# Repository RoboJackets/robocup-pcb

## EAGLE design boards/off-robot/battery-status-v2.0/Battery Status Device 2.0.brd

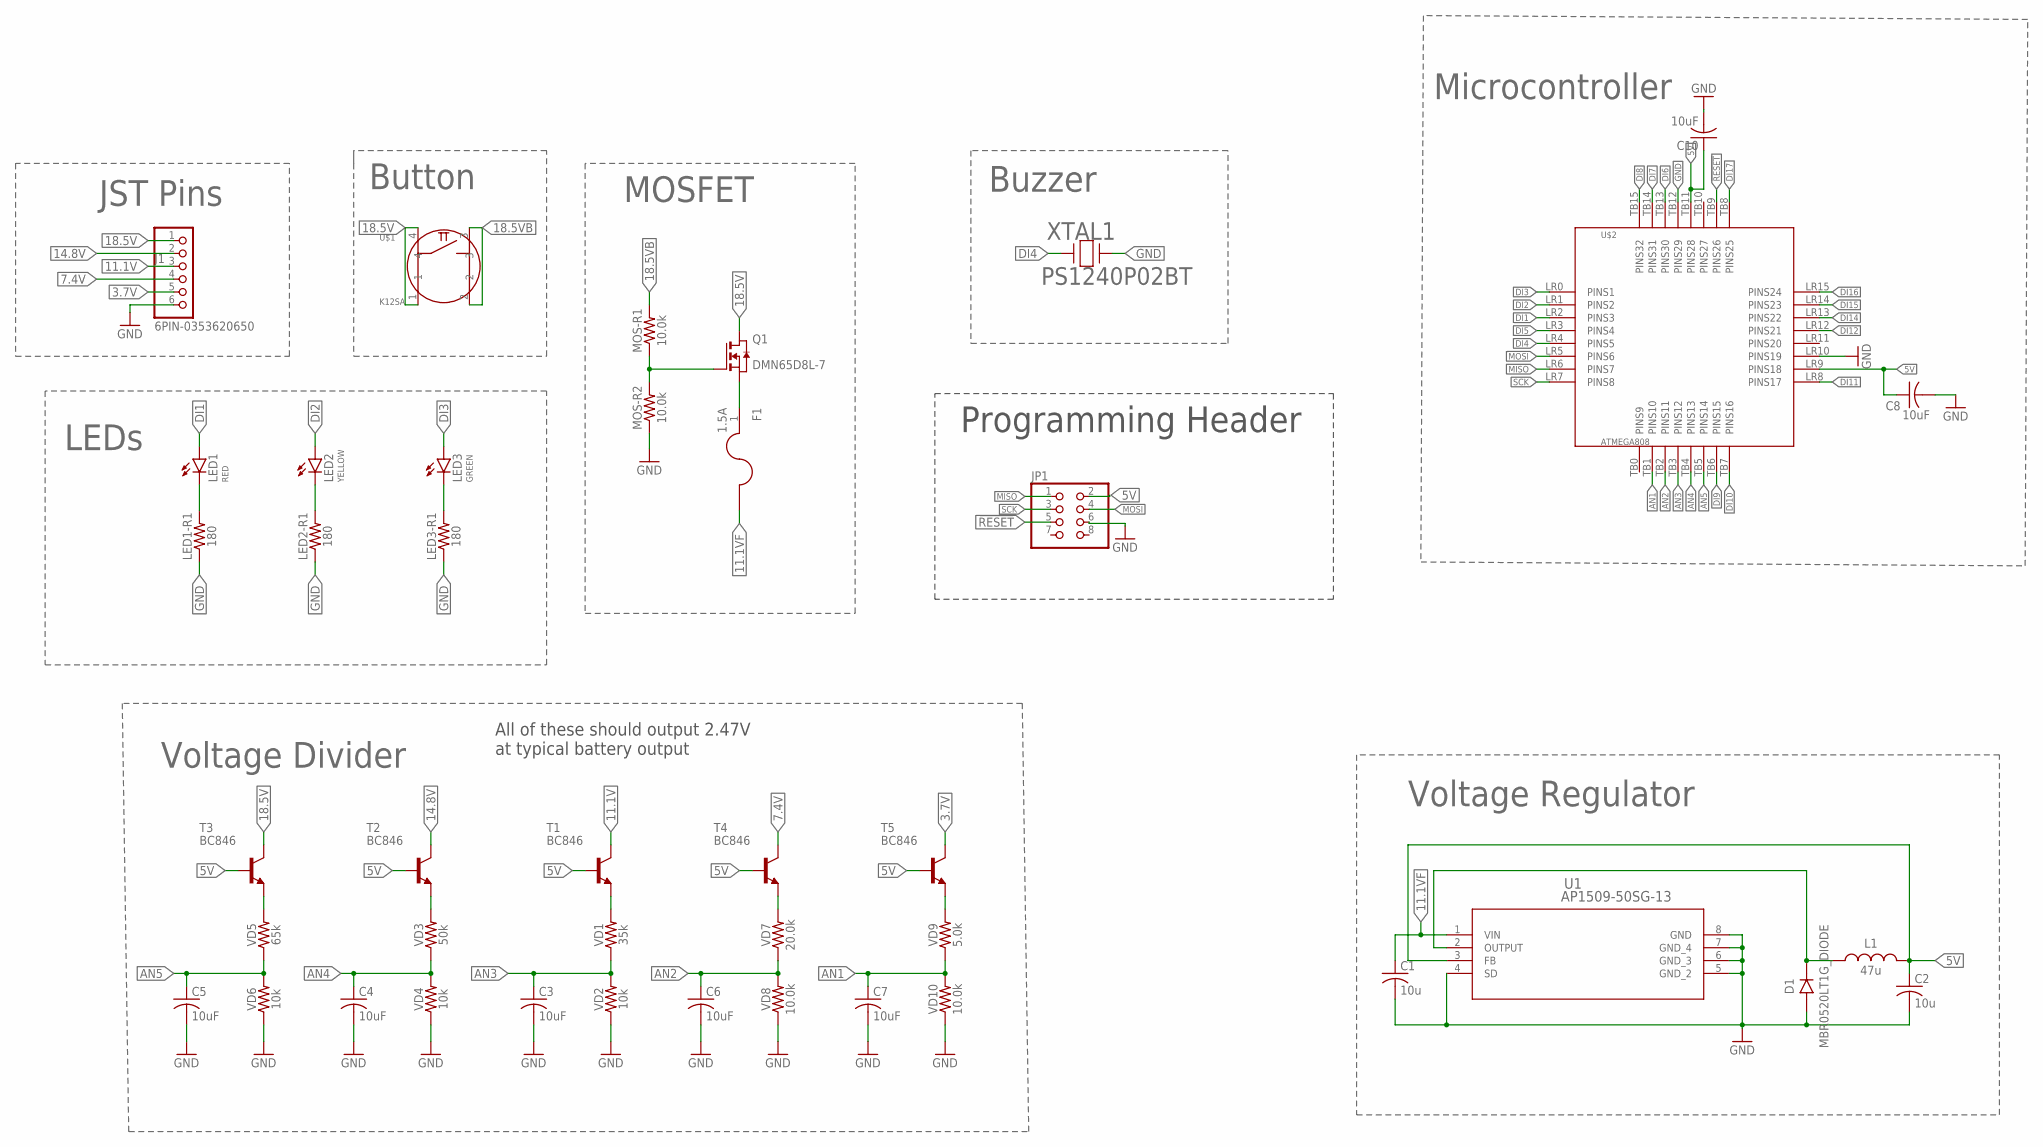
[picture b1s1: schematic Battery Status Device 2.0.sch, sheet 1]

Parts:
C1, C2: 10u; C0805
C3, C4, C5, C6, C7, C8, C10: 10uF; C0805
D1: MBR0520LT1G_DIODE; SOD-123
F1: 1.5A; F1206
J1: 6PIN-0353620650; 0353620650
JP1: PINHD-2X4; 2X04
L1: 47u; 0805
LED1: RED; LED5MM
LED1-R1, LED2-R1, LED3-R1: 180; 0603
LED2: YELLOW; LED5MM
LED3: GREEN; LED5MM
MOS-R1, MOS-R2: 10.0k; 0603
Q1: DMN65D8L-7; SOT-23-3
T1, T2, T3, T4, T5: BC846; SOT23
U1: AP1509-50SG-13; SOP-8L_DIO
U$1: K12SA
U$2: ATMEGA808
VD1: 35k; 0603
VD2, VD4, VD6: 10k; 0603
VD3: 50k; 0603
VD5: 65k; 0603
VD7: 20.0k; 0603
VD8, VD10: 10.0k; 0603
VD9: 5.0k; 0603
XTAL1: PS1240P02BT; XTAL_PS1240P02BT_TDK

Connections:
3.7V: J1.5, T5.3 (C)
5V: C2.1, C8.1, C10.1, JP1.2, L1.2, T1.1 (B), T2.1 (B), T3.1 (B), T4.1 (B), T5.1 (B), U1.3 (FB), U$2.LR9 (PINS18), U$2.TB11 (PINS28); also elsewhere on the board
7.4V: J1.4, T4.3 (C)
11.1V: J1.3, T1.3 (C)
11.1VF: C1.1, F1.2, U1.1 (VIN)
14.8V: J1.2, T2.3 (C)
18.5V: J1.1, Q1.3 (D), T3.3 (C), U$1.1, U$1.4
18.5VB: MOS-R1.2, U$1.2, U$1.3
!RESET!: JP1.5, U$2.TB9 (PINS26)
AN1: C7.1, U$2.TB1 (PINS10), VD9.1, VD10.2
AN2: C6.1, U$2.TB2 (PINS11), VD7.1, VD8.2
AN3: C3.1, U$2.TB3 (PINS12), VD1.1, VD2.2
AN4: C4.1, U$2.TB4 (PINS13), VD3.1, VD4.2
AN5: C5.1, U$2.TB5 (PINS14), VD5.1, VD6.2
DI1: LED1.A, U$2.LR2 (PINS3)
DI2: LED2.A, U$2.LR1 (PINS2)
DI3: LED3.A, U$2.LR0 (PINS1)
DI4: U$2.LR4 (PINS5), XTAL1.1
DI5: U$2.LR3 (PINS4); also elsewhere on the board
DI6: U$2.TB13 (PINS30); also elsewhere on the board
DI7: U$2.TB14 (PINS31); also elsewhere on the board
DI8: U$2.TB15 (PINS32); also elsewhere on the board
DI9: U$2.TB6 (PINS15); also elsewhere on the board
DI10: U$2.TB7 (PINS16); also elsewhere on the board
DI11: U$2.LR8 (PINS17); also elsewhere on the board
DI12: U$2.LR12 (PINS21); also elsewhere on the board
DI14: U$2.LR13 (PINS22); also elsewhere on the board
DI15: U$2.LR14 (PINS23); also elsewhere on the board
DI16: U$2.LR15 (PINS24); also elsewhere on the board
DI17: U$2.TB8 (PINS25); also elsewhere on the board
GND: C1.2, C2.2, C3.2, C4.2, C5.2, C6.2, C7.2, C8.2, C10.2, D1.2 (A), J1.6, JP1.6, LED1-R1.1, LED2-R1.1, LED3-R1.1, MOS-R2.1, U1.4 (SD), U1.5 (GND_2), U1.6 (GND_3), U1.7 (GND_4), U1.8 (GND), U$2.LR10 (PINS19), U$2.TB12 (PINS29), VD2.1, VD4.1, VD6.1, VD8.1, VD10.1, XTAL1.2; also elsewhere on the board
MISO: JP1.1, U$2.LR6 (PINS7)
MOSI: JP1.4, U$2.LR5 (PINS6)
unnamed: D1.1 (C), L1.1, U1.2 (OUTPUT)
unnamed: LED1.K (C), LED1-R1.2
unnamed: LED2.K (C), LED2-R1.2
unnamed: LED3.K (C), LED3-R1.2
unnamed: T5.2 (E), VD9.2
unnamed: T4.2 (E), VD7.2
unnamed: T1.2 (E), VD1.2
unnamed: MOS-R1.1, MOS-R2.2, Q1.1 (G)
unnamed: T2.2 (E), VD3.2
unnamed: F1.1, Q1.2 (S)
unnamed: T3.2 (E), VD5.2
SCK: JP1.3, U$2.LR7 (PINS8)

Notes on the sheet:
Microcontroller
Voltage Regulator
Voltage Divider
JST Pins
Button
Buzzer
LEDs
Programming Header
MOSFET
All of these should output 2.47V at typical battery output

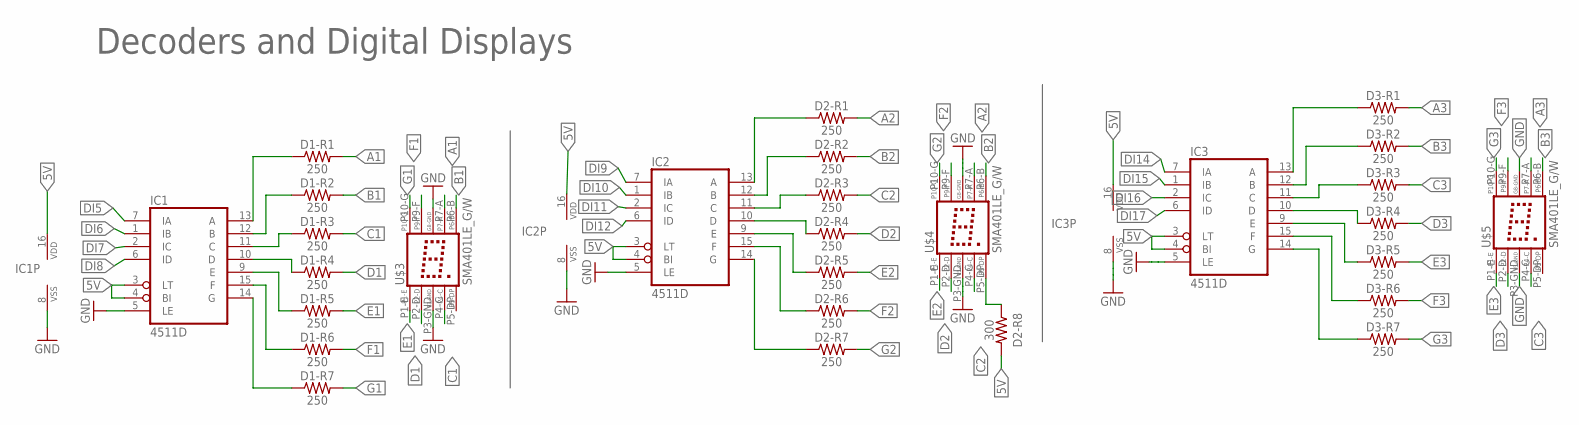
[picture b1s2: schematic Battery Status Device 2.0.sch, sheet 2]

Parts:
D1-R1, D1-R2, D1-R3, D1-R4, D1-R5, D1-R6, D1-R7, D2-R1, D2-R2, D2-R3, D2-R4, D2-R5, D2-R6, D2-R7, D3-R1, D3-R2, D3-R3, D3-R4, D3-R5, D3-R6, D3-R7: 250; 0603
D2-R8: 300; 0603
IC1, IC2, IC3: 4511D; SO16
U$3, U$4, U$5: SMA401LE_G/W

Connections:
5V: D2-R8.2, IC1.3 (LT), IC1.4 (BI), IC1.16 (VDD), IC2.3 (LT), IC2.4 (BI), IC2.16 (VDD), IC3.3 (LT), IC3.4 (BI), IC3.16 (VDD); also elsewhere on the board
A1: D1-R1.2, U$3.P7-A
A2: D2-R1.2, U$4.P7-A
A3: D3-R1.2, U$5.P7-A
B1: D1-R2.2, U$3.P6-B
B2: D2-R2.2, U$4.P6-B
B3: D3-R2.2, U$5.P6-B
C1: D1-R3.2, U$3.P4-C
C2: D2-R3.2, U$4.P4-C
C3: D3-R3.2, U$5.P4-C
D1: D1-R4.2, U$3.P2-D
D2: D2-R4.2, U$4.P2-D
D3: D3-R4.2, U$5.P2-D
DI5: IC1.7 (IA); also elsewhere on the board
DI6: IC1.1 (IB); also elsewhere on the board
DI7: IC1.2 (IC); also elsewhere on the board
DI8: IC1.6 (ID); also elsewhere on the board
DI9: IC2.7 (IA); also elsewhere on the board
DI10: IC2.1 (IB); also elsewhere on the board
DI11: IC2.2 (IC); also elsewhere on the board
DI12: IC2.6 (ID); also elsewhere on the board
DI14: IC3.7 (IA); also elsewhere on the board
DI15: IC3.1 (IB); also elsewhere on the board
DI16: IC3.2 (IC); also elsewhere on the board
DI17: IC3.6 (ID); also elsewhere on the board
E1: D1-R5.2, U$3.P1-E
E2: D2-R5.2, U$4.P1-E
E3: D3-R5.2, U$5.P1-E
F1: D1-R6.2, U$3.P9-F
F2: D2-R6.2, U$4.P9-F
F3: D3-R6.2, U$5.P9-F
G1: D1-R7.2, U$3.P10-G
G2: D2-R7.2, U$4.P10-G
G3: D3-R7.2, U$5.P10-G
GND: IC1.5 (LE), IC1.8 (VSS), IC2.5 (LE), IC2.8 (VSS), IC3.5 (LE), IC3.8 (VSS), U$3.P3-GND, U$3.P8-GND, U$4.P3-GND, U$4.P8-GND, U$5.P3-GND, U$5.P8-GND; also elsewhere on the board
unnamed: D1-R1.1, IC1.13 (A)
unnamed: D1-R2.1, IC1.12 (B)
unnamed: D1-R3.1, IC1.11 (C)
unnamed: D1-R4.1, IC1.10 (D)
unnamed: D1-R6.1, IC1.15 (F)
unnamed: D1-R5.1, IC1.9 (E)
unnamed: D1-R7.1, IC1.14 (G)
unnamed: D2-R1.1, IC2.13 (A)
unnamed: D2-R2.1, IC2.12 (B)
unnamed: D2-R3.1, IC2.11 (C)
unnamed: D2-R4.1, IC2.10 (D)
unnamed: D2-R5.1, IC2.9 (E)
unnamed: D2-R6.1, IC2.15 (F)
unnamed: D2-R7.1, IC2.14 (G)
unnamed: D3-R1.1, IC3.13 (A)
unnamed: D3-R2.1, IC3.12 (B)
unnamed: D3-R3.1, IC3.11 (C)
unnamed: D3-R4.1, IC3.10 (D)
unnamed: D3-R5.1, IC3.9 (E)
unnamed: D3-R6.1, IC3.15 (F)
unnamed: D3-R7.1, IC3.14 (G)
unnamed: D2-R8.1, U$4.P5-DP

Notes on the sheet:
Decoders and Digital Displays

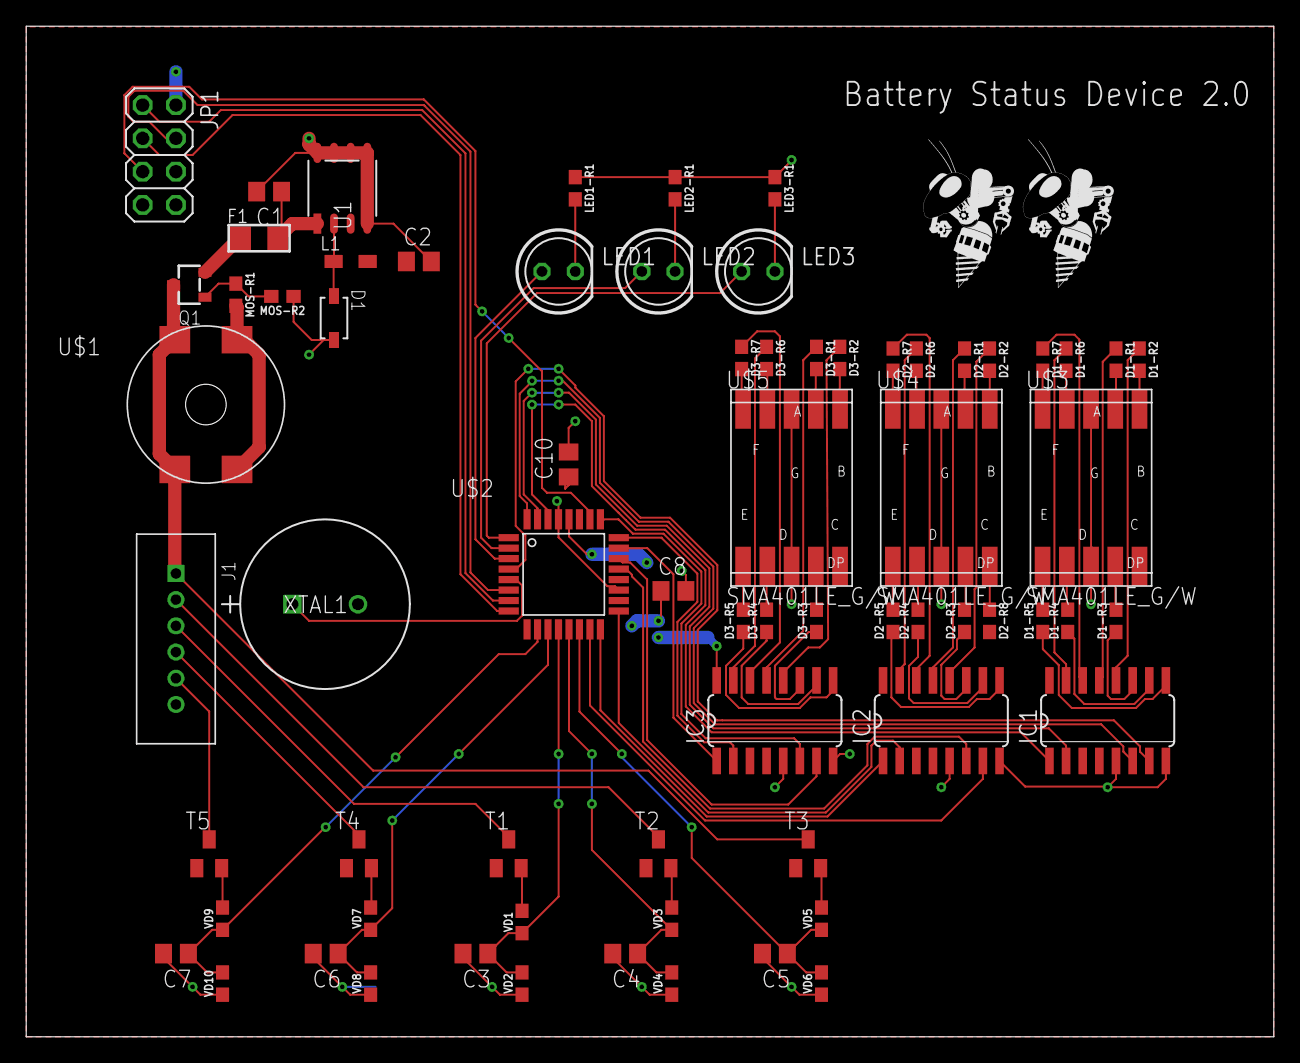
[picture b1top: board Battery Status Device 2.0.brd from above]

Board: 2 copper layers, 95.2 x 77.1 mm, 72 parts (0 on the bottom side), 88 nets.

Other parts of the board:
U$6, U$7: ROBOBUZZ_0.6X

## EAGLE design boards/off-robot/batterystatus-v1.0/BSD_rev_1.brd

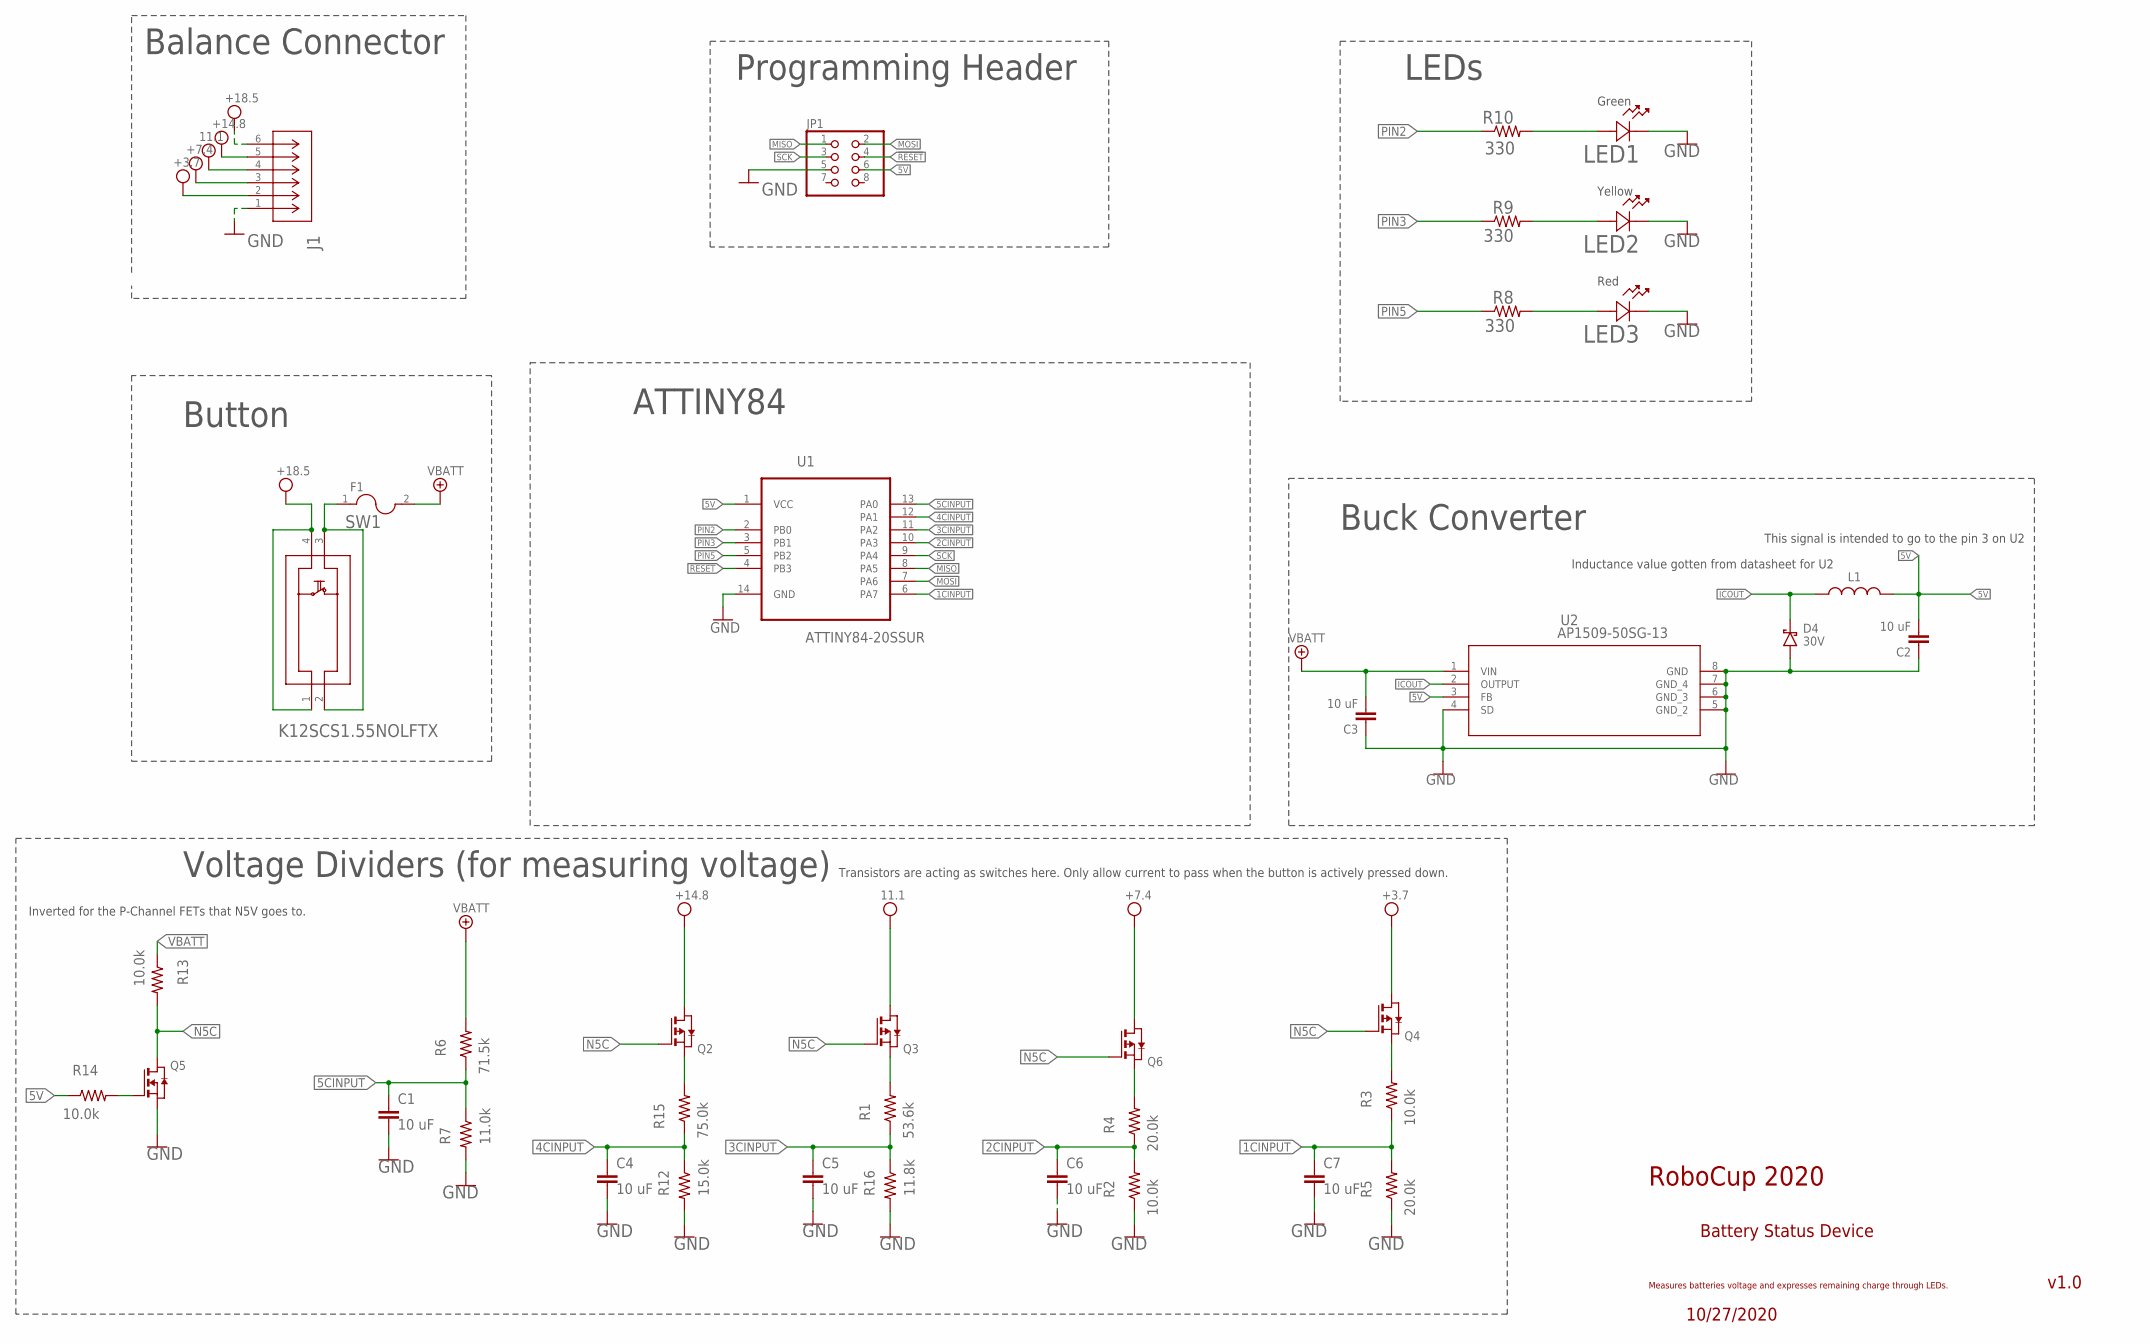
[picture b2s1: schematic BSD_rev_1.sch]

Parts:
C1, C2, C3, C4, C5, C6, C7: 10 uF; C0603
D4: 30V; POWERDI-123
F1: 0698Q5000-01; FUSE_0698Q5000-01
J1: B6B-XH-A(LF)(SN); CONN_B6B-XH-A(LF)(SN)_JST
JP1: PINHD-2X4; 2X04
L1: 48470SC
LED1, LED2, LED3: SLR-56VC3F; LED_SLR-56_ROM
Q2, Q3, Q4, Q6: SOT233; SOT-23_DIO-L
Q5: LND150K1-G; SOT-23-3
R1: 53.6k; R0603
R2, R3, R13, R14: 10.0k; R0603
R4, R5: 20.0k; R0603
R6: 71.5k; R0603
R7: 11.0k; R0603
R8, R9, R10: 330; R0603
R12: 15.0k; R0603
R15: 75.0k; R0603
R16: 11.8k; R0603
SW1: K12SCS1.55NOLFTX
U1: ATTINY84-20SSUR; SOIC127P600X175-14N
U2: AP1509-50SG-13; SOP-8L_DIO

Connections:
1C: J1.2, Q4.3 (D)
1CINPUT: C7.2, R3.1, R5.2, U1.6 (PA7)
2C: J1.3, Q6.3 (D)
2CINPUT: C6.2, R2.2, R4.1, U1.10 (PA3)
3C: J1.4, Q3.3 (D)
3CINPUT: C5.2, R1.1, R16.1, U1.11 (PA2)
4C: J1.5, Q2.3 (D)
4CINPUT: C4.2, R12.1, R15.1, U1.12 (PA1)
5C: J1.6, SW1.1, SW1.4
5CINPUT: C1.2, R6.1, R7.1, U1.13 (PA0)
5V: C2.2, JP1.6, L1.P$2 (2), R14.1, U1.1 (VCC), U2.3 (FB)
!RESET!: JP1.4, U1.4 (PB3)
GLED: LED1.2, R10.2
GND: C1.1, C2.1, C3.1, C4.1, C5.1, C6.1, C7.1, D4.A, J1.1, JP1.5, LED1.1, LED2.1, LED3.1, Q5.3 (S), R2.1, R5.1, R7.2, R12.2, R16.2, U1.14 (GND), U2.4 (SD), U2.5 (GND_2), U2.6 (GND_3), U2.7 (GND_4), U2.8 (GND)
ICOUT: D4.C, L1.P$1 (1), U2.2 (OUTPUT)
IDK: Q5.1 (G), R14.2
MISO: JP1.1, U1.8 (PA5)
MOSI: JP1.2, U1.7 (PA6)
N5C: Q2.1 (G), Q3.1 (G), Q4.1 (G), Q5.2 (D), Q6.1 (G), R13.2
unnamed: Q6.2 (S), R4.2
unnamed: Q4.2 (S), R3.2
unnamed: Q2.2 (S), R15.2
unnamed: Q3.2 (S), R1.2
PIN2: R10.1, U1.2 (PB0)
PIN3: R9.1, U1.3 (PB1)
PIN5: R8.1, U1.5 (PB2)
RLED: LED3.2, R8.2
SCK: JP1.3, U1.9 (PA4)
VBATT: C3.2, F1.2, R6.2, R13.1, U2.1 (VIN)
VBATTB: F1.1, SW1.2, SW1.3
YLED: LED2.2, R9.2

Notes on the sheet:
RoboCup 2020
Battery Status Device
Measures batteries voltage and expresses remaining charge through LEDs.
v1.0
10/27/2020
LEDs
ATTINY84
Button
Balance Connector
Buck Converter
This signal is intended to go to the pin 3 on U2
Programming Header
Voltage Dividers (for measuring voltage)
Transistors are acting as switches here. Only allow current to pass when the button is actively pressed down.
Inductance value gotten from datasheet for U2
Green
Red
Yellow
Inverted for the P-Channel FETs that N5V goes to.

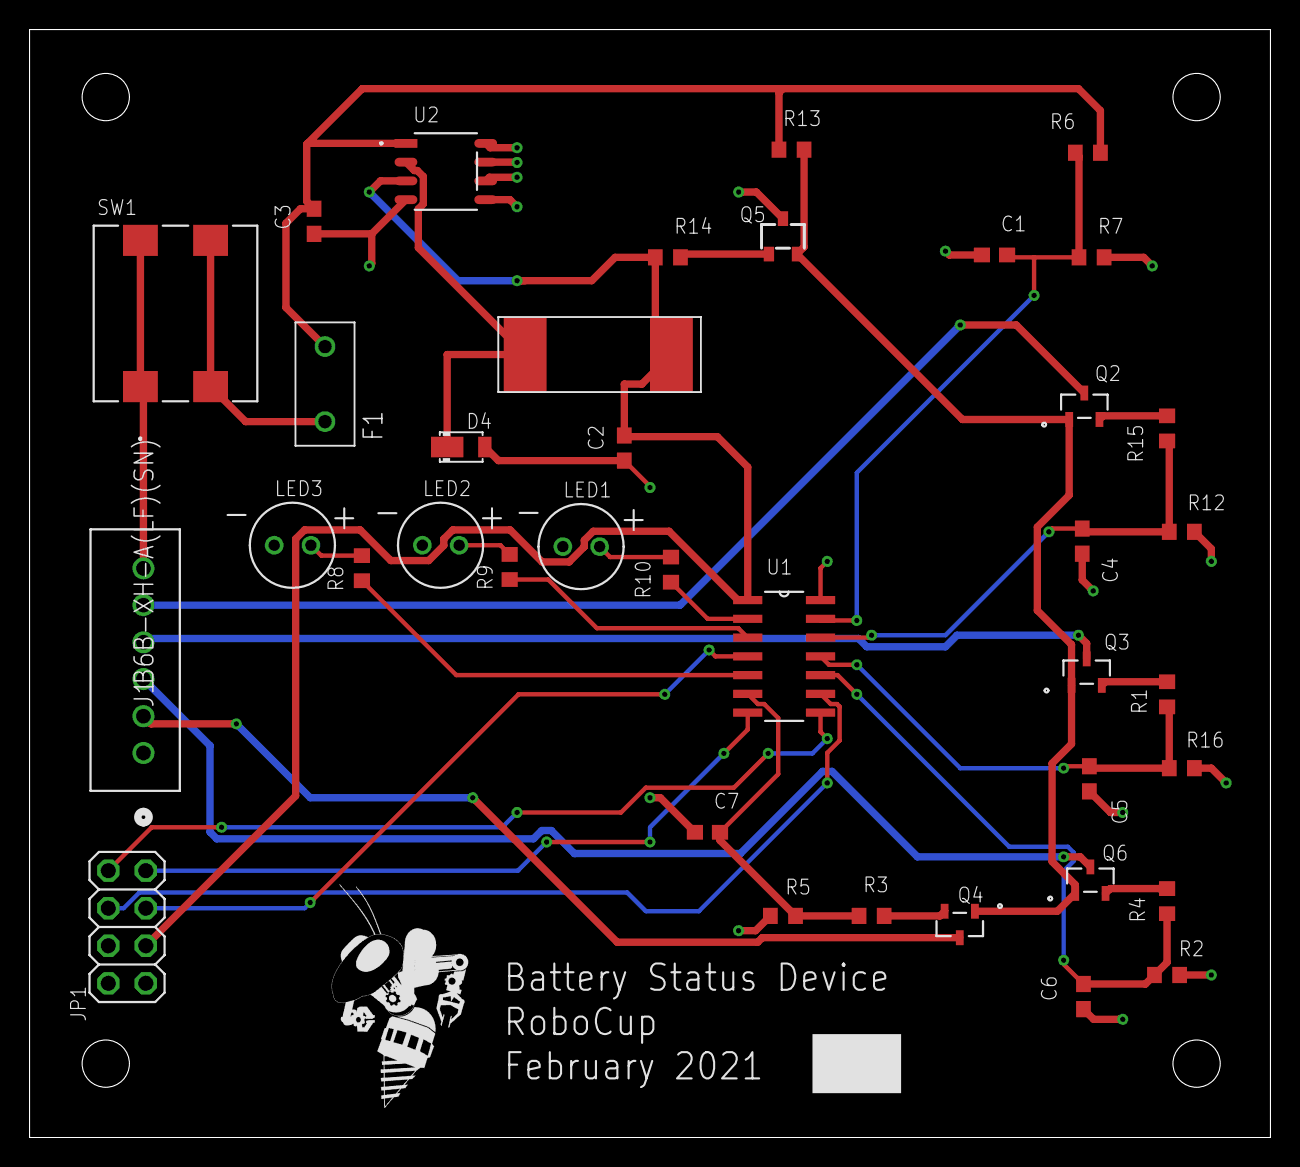
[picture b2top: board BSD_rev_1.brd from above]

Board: 2 copper layers, 84.0 x 75.0 mm, 39 parts (0 on the bottom side), 31 nets.

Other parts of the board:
U$2: ROBOBUZZ_0.8X

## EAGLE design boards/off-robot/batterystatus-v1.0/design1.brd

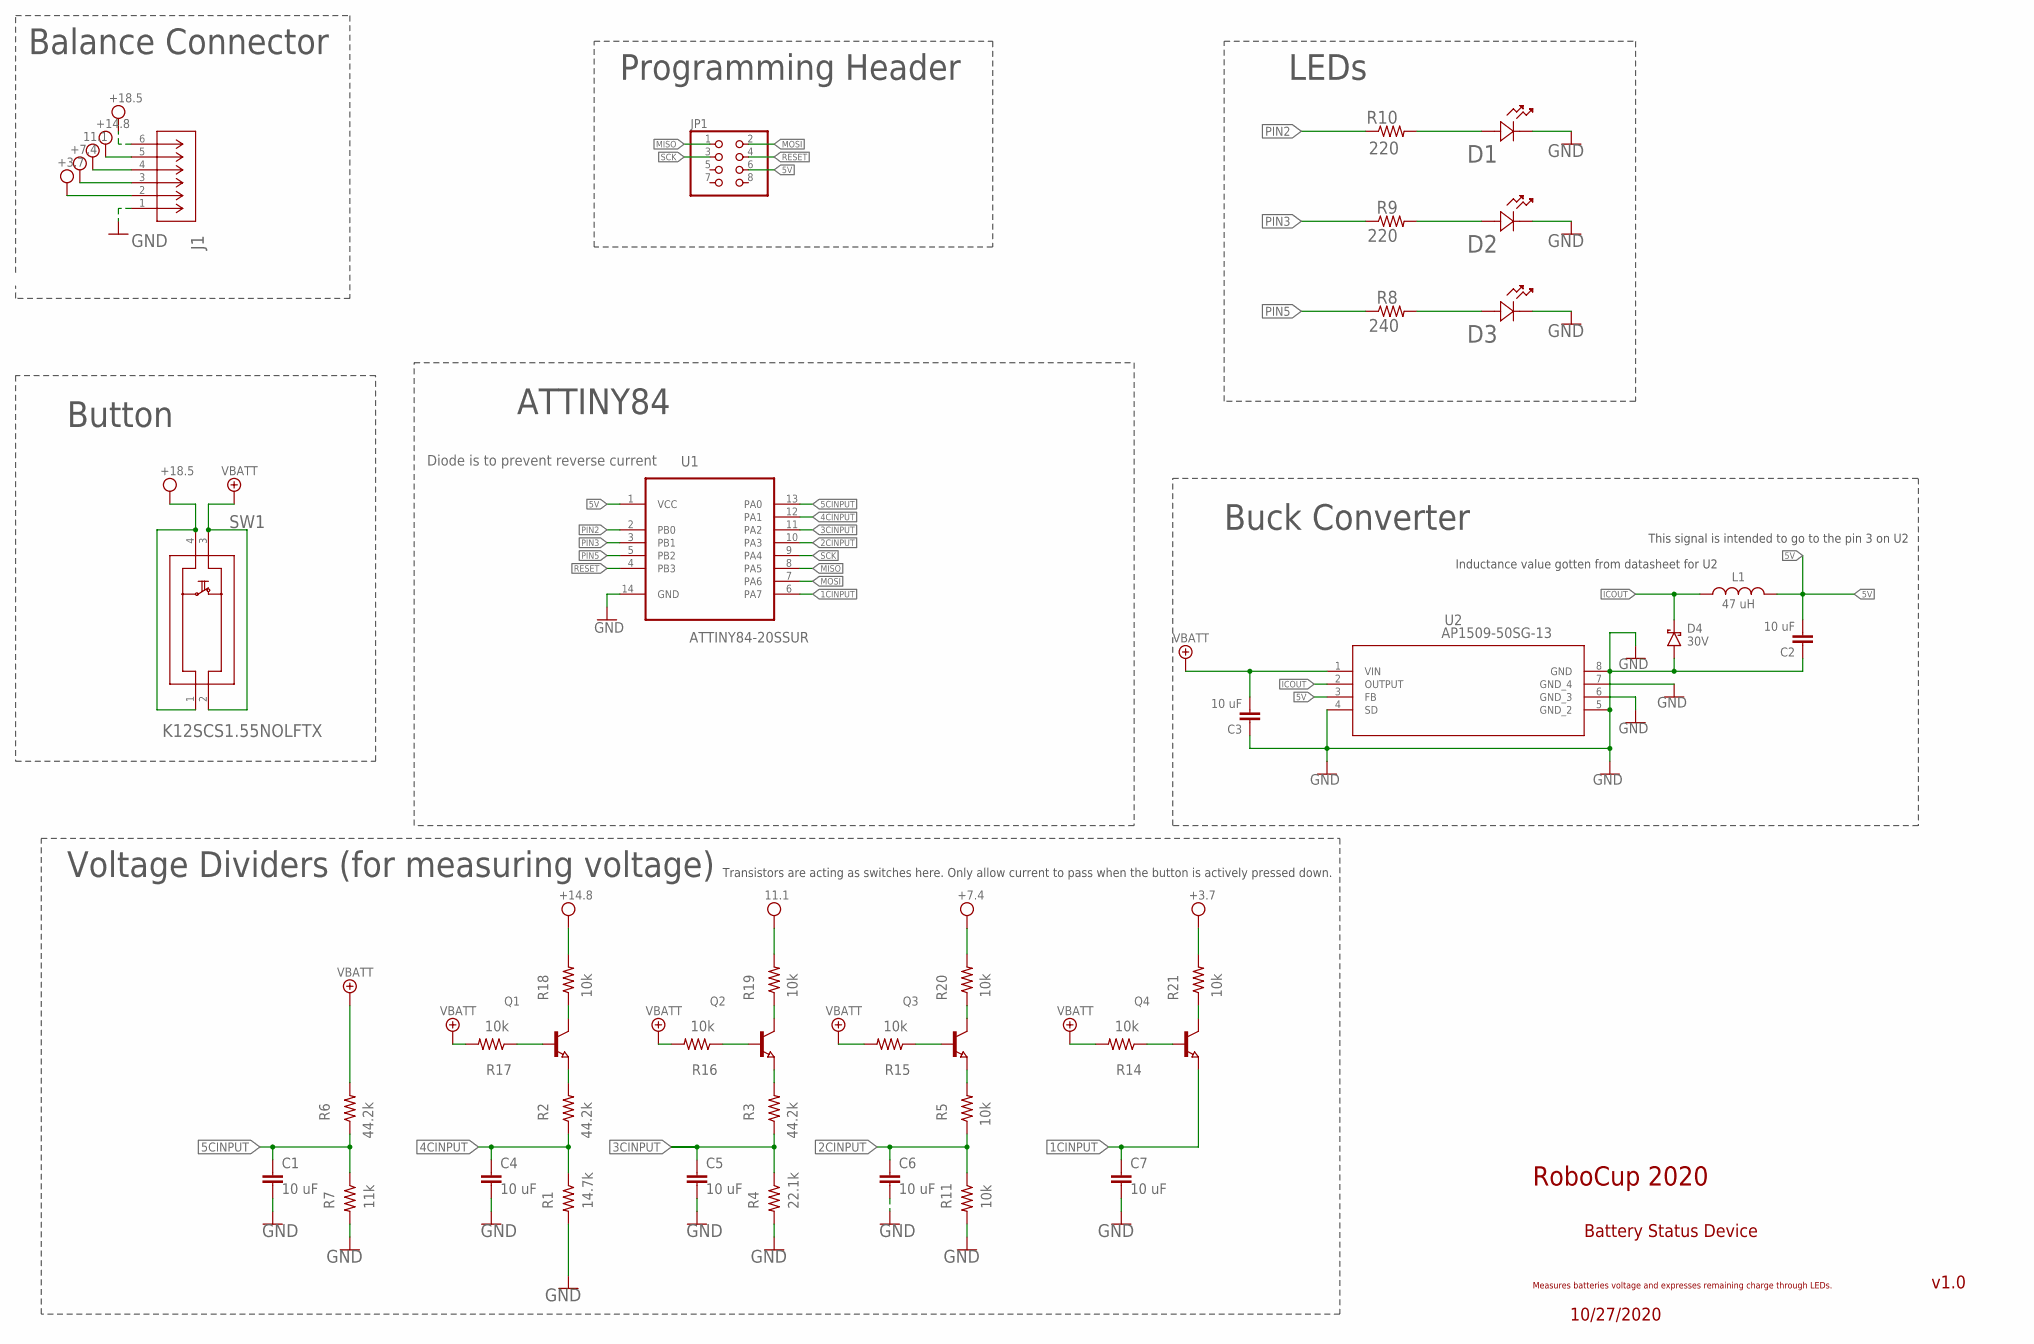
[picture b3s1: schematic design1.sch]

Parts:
C1, C2, C3, C4, C5, C6, C7: 10 uF; C0603
D1, D2, D3: SLR-56VC3F; LED_SLR-56_ROM
D4: 30V; POWERDI-123
J1: B6B-XH-A(LF)(SN); CONN_B6B-XH-A(LF)(SN)_JST
JP1: PINHD-2X4; 2X04
L1: 47 uH; 48470SC
Q1, Q2, Q3, Q4: NPN-TRANSISTOR_SOT23; SOT23
R1: 14.7k; R0603
R2, R3, R6: 44.2k; R0603
R4: 22.1k; R0603
R5, R11, R14, R15, R16, R17, R18, R19, R20, R21: 10k; R0603
R7: 11k; R0603
R8: 240; R0603
R9, R10: 220; R0603
SW1: K12SCS1.55NOLFTX
U1: ATTINY84-20SSUR; SOIC127P600X175-14N
U2: AP1509-50SG-13; SOP-8L_DIO

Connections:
1C: J1.2, R21.2
1CINPUT: C7.2, Q4.2 (E), U1.6 (PA7)
2C: J1.3, R20.2
2CINPUT: C6.2, R5.1, R11.1, U1.10 (PA3)
3C: J1.4, R19.2
3CINPUT: C5.2, R3.1, R4.1, U1.11 (PA2)
4C: J1.5, R18.2
4CINPUT: C4.2, R1.1, R2.1, U1.12 (PA1)
5C: J1.6, SW1.1, SW1.4
5CINPUT: C1.2, R6.1, R7.1, U1.13 (PA0)
5V: C2.2, JP1.6, L1.P$2 (2), U1.1 (VCC), U2.3 (FB)
GLED: D1.2, R10.2
GND: C1.1, C2.1, C3.1, C4.1, C5.1, C6.1, C7.1, D1.1, D2.1, D3.1, D4.A, J1.1, R1.2, R4.2, R7.2, R11.2, U1.14 (GND), U2.4 (SD), U2.5 (GND_2), U2.6 (GND_3), U2.7 (GND_4), U2.8 (GND)
ICOUT: D4.C, L1.P$1 (1), U2.2 (OUTPUT)
MISO: JP1.1, U1.8 (PA5)
MOSI: JP1.2, U1.7 (PA6)
unnamed: Q1.2 (E), R2.2
unnamed: Q2.2 (E), R3.2
unnamed: Q3.2 (E), R5.2
unnamed: Q1.3 (C), R18.1
unnamed: Q2.3 (C), R19.1
unnamed: Q3.3 (C), R20.1
unnamed: Q4.3 (C), R21.1
PIN2: R10.1, U1.2 (PB0)
PIN3: R9.1, U1.3 (PB1)
PIN5: R8.1, U1.5 (PB2)
RESET: JP1.4, U1.4 (PB3)
RLED: D3.2, R8.2
SCK: JP1.3, U1.9 (PA4)
TOT1: Q1.1 (B), R17.1
TOT2: Q2.1 (B), R16.1
TOT3: Q3.1 (B), R15.1
TOT4: Q4.1 (B), R14.1
VBATT: C3.2, R6.2, R14.2, R15.2, R16.2, R17.2, SW1.2, SW1.3, U2.1 (VIN)
YLED: D2.2, R9.2

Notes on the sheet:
RoboCup 2020
Battery Status Device
Measures batteries voltage and expresses remaining charge through LEDs.
v1.0
10/27/2020
LEDs
ATTINY84
Button
Balance Connector
Buck Converter
This signal is intended to go to the pin 3 on U2
Programming Header
Diode is to prevent reverse current
Voltage Dividers (for measuring voltage)
Transistors are acting as switches here. Only allow current to pass when the button is actively pressed down.
Inductance value gotten from datasheet for U2

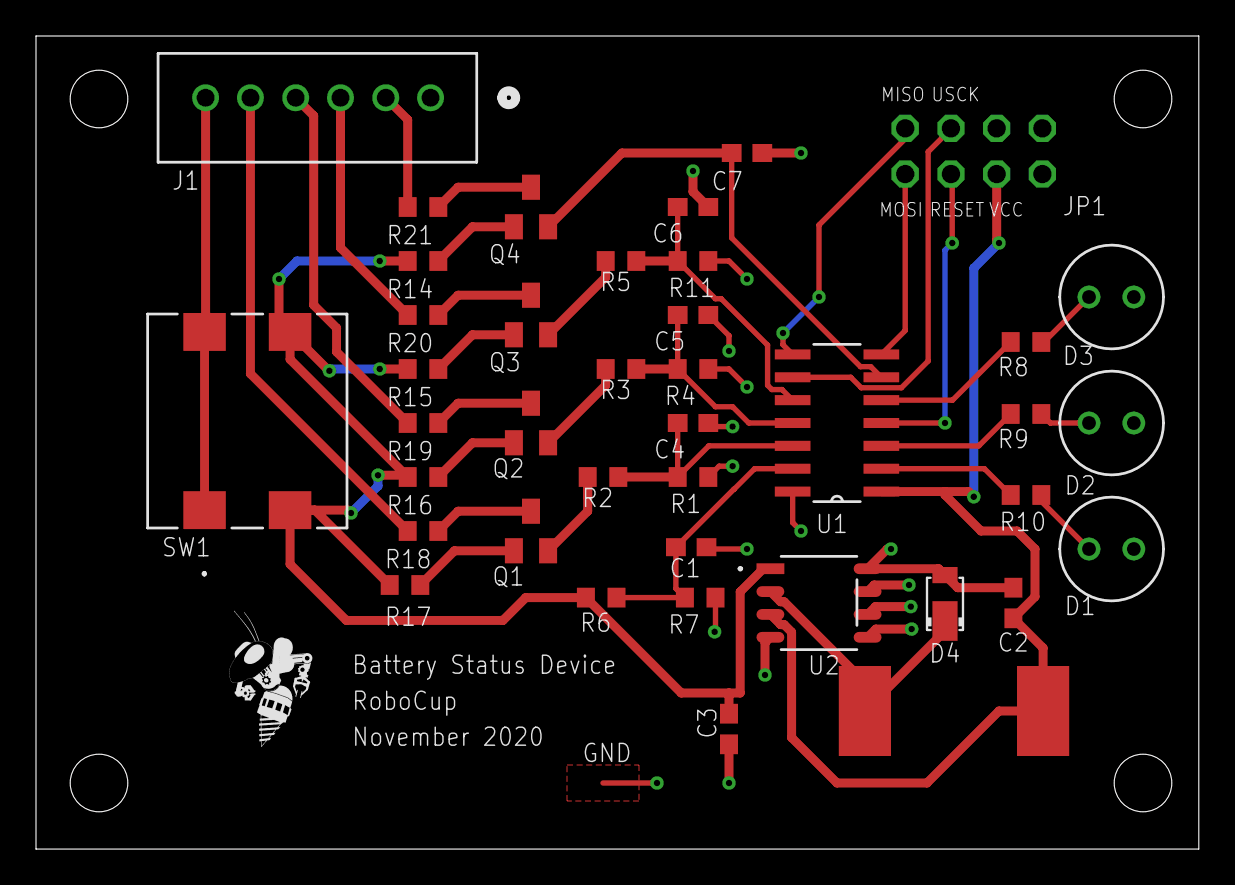
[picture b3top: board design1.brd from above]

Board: 2 copper layers, 64.6 x 45.2 mm, 41 parts (1 on the bottom side), 35 nets.

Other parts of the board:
U$2: ROBOBUZZ_0.4X

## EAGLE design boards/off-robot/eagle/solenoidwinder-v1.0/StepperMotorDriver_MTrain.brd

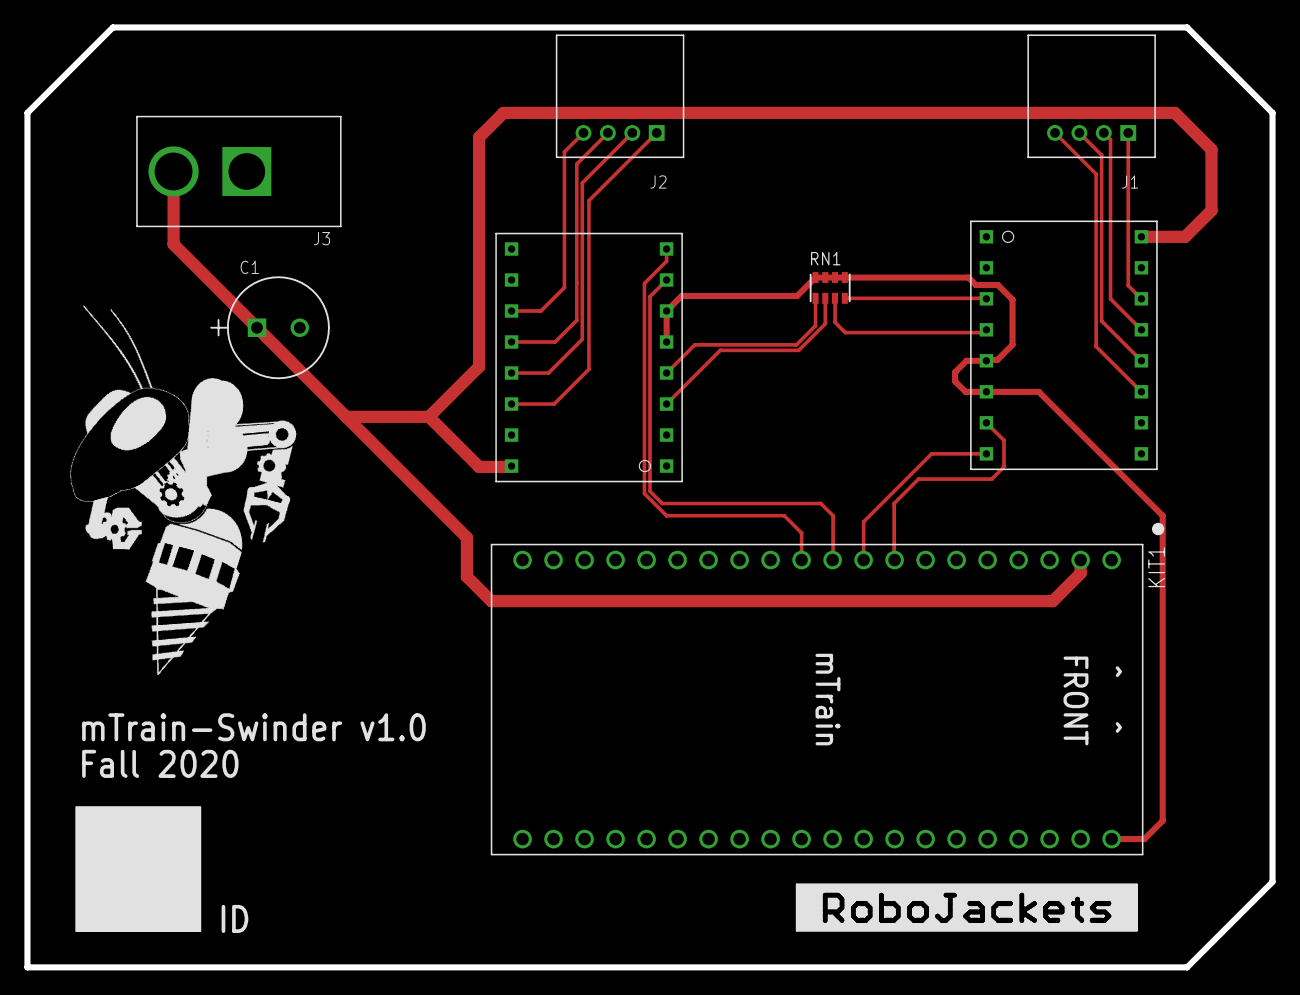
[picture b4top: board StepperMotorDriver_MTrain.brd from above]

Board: 2 copper layers, 102.0 x 77.0 mm, 10 parts (0 on the bottom side), 19 nets.

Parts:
C1: ECA-0JM102; PCAP_8X112
J1, J2: 4-PIN_2MM-H; 2MM-4-H
J3: PJ-037A
KIT1: MTRAIN; MTRAIN-KIT
RN1: RA-4_1206
U$1, U$2: DRV8825
U$3: ROBOJACKETS
U$5: ROBOBUZZ_1.4X

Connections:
+3.3V: KIT1.VDD, RN1.2, RN1.4, RN1.6, RN1.8, U$1.5, U$1.6, U$2.5, U$2.6
DIR1: KIT1.P$9, U$1.8
DIR2: KIT1.P$11, U$2.8
GND: C1.2, J3.P$1, KIT1.GND, U$1.10, U$1.16, U$2.10, U$2.16
unnamed: RN1.7, U$1.3
unnamed: RN1.5, U$1.4
unnamed: RN1.3, U$2.3
unnamed: RN1.1, U$2.4
unnamed: J1.1, U$1.11
unnamed: J1.2, U$1.12
unnamed: J1.3, U$1.13
unnamed: J1.4, U$1.14
unnamed: J2.1, U$2.11
unnamed: J2.2, U$2.12
unnamed: J2.3, U$2.13
unnamed: J2.4, U$2.14
STEP1: KIT1.P$8, U$1.7
STEP2: KIT1.P$10, U$2.7
VBATT: C1.1, J3.P$2, KIT1.VIN, U$1.9, U$2.9

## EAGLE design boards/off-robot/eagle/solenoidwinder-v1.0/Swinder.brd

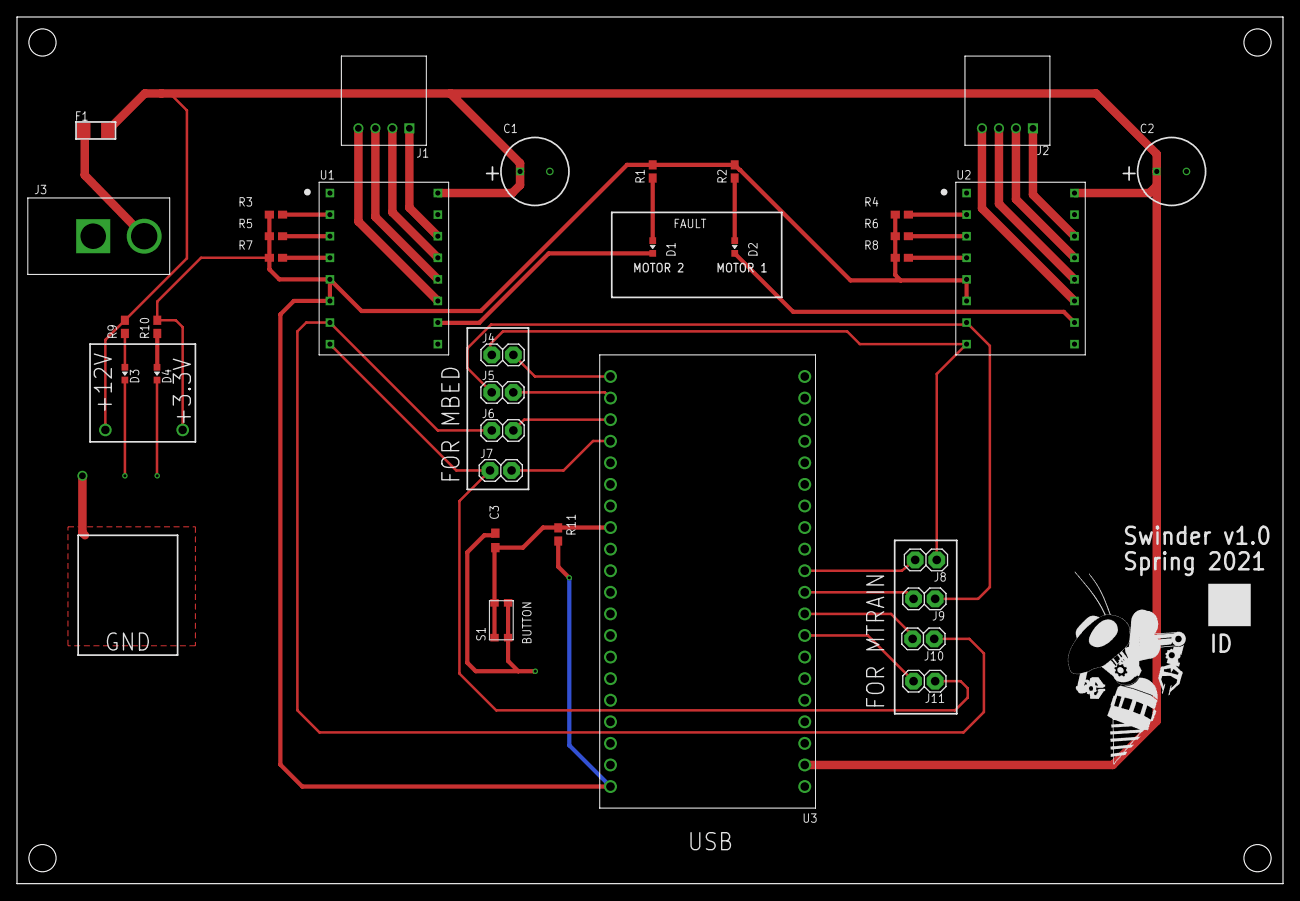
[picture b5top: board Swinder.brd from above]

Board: 2 copper layers, 149.0 x 102.0 mm, 35 parts (0 on the bottom side), 37 nets.

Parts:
C1, C2: UKL1E101KPDANATD
C3: 0.1uF; C0603
D1, D2: RED; CHIP-LED0603
D3, D4: GREEN; CHIP-LED0603
F1: 4.5 A; F1206
J1, J2: 4PIN-0353630460; 0353630460
J3: PJ-037A
J4, J5, J6, J7, J8, J9, J10, J11: 1X2
R1, R2, R9, R10: 1K; R0603W
R3, R4, R5, R6, R7, R8: 0; R0603W
R11: 10K; R0603W
S1: KMR2
U1, U2: DRV8825
U3: MBED_NXP_LPC1768; MBED-KIT
U$1: ROBOBUZZ_1.2X

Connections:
+3.3V: R1.2, R2.2, R3.1, R4.1, R5.1, R6.1, R7.1, R8.1, R10.2, R11.2, U1.5, U1.6, U2.5, U2.6, U3.VOUT
+12V: C1.+, C2.+, F1.2, R9.2, U1.9, U2.9, U3.VIN
A1$1: J2.3, U2.13
A1$2: J1.3, U1.13
A2$1: J2.4, U2.14
A2$2: J1.4, U1.14
B1$1: J2.2, U2.12
B1$2: J1.2, U1.12
B2$1: J2.1, U2.11
B2$2: J1.1, U1.11
DIR1: J4.1, J8.1, U2.8
DIR1A: J4.2, U3.P$21
DIR1B: J8.2, U3.P$11
DIR2: J7.1, J11.1, U1.8
DIR2A: J7.2, U3.P$24
DIR2B: J11.2, U3.P$8
FPOW: F1.1, J3.P$2
G1: D3.A, R9.1
G2: D4.A, R10.1
GND: C1.-, C2.-, C3.2, D3.C, D4.C, J3.P$1, S1.2.1, S1.2.2, U1.10, U1.16, U2.10, U2.16, U3.GND
M0-1: R4.2, U2.2
M0-2: R3.2, U1.2
M1-1: R6.2, U2.3
M1-2: R5.2, U1.3
M2-1: R8.2, U2.4
M2-2: R7.2, U1.4
unnamed: C3.1, R11.1, S1.1.1, S1.1.2, U3.P$28
R1-1: D2.A, R2.1
R1-2: D2.C, U2.15
R2-1: D1.A, R1.1
R2-2: D1.C, U1.15
STEP1: J5.1, J9.1, U2.7
STEP1A: J5.2, U3.P$22
STEP1B: J9.2, U3.P$10
STEP2: J6.1, J10.1, U1.7
STEP2A: J6.2, U3.P$23
STEP2B: J10.2, U3.P$9

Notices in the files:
parts and their libraries:
COPYRIGHT: Copyright (C) 2021 Ultra Librarian. All rights reserved.
COPYRIGHT: Copyright (C) 2018 Accelerated Designs. All rights reserved
